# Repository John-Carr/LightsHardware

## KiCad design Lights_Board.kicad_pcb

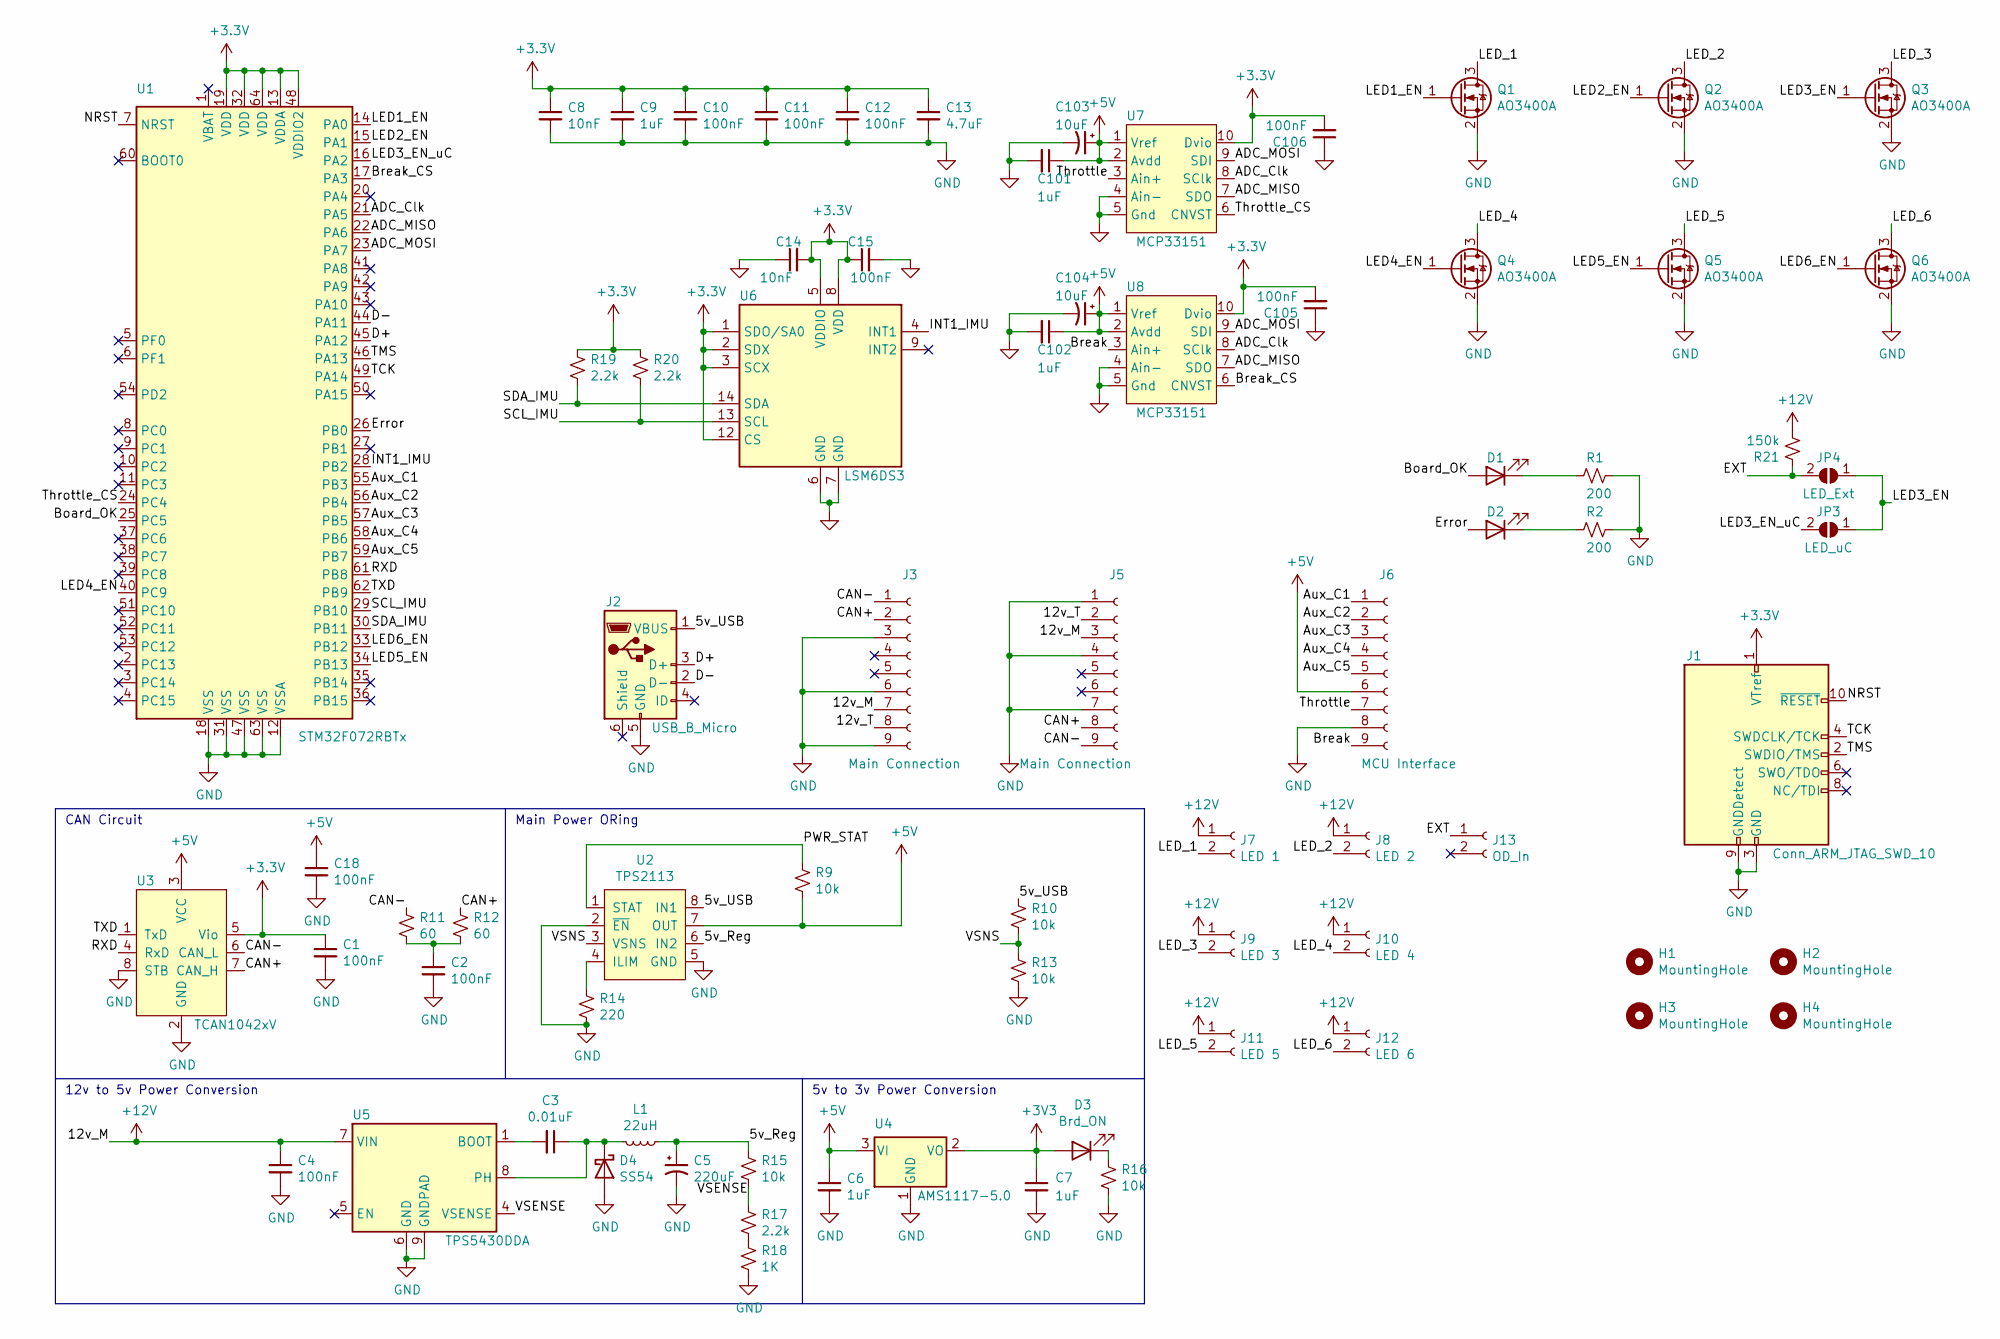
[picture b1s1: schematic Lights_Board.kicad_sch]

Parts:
C1, C2, C4, C10, C11, C12, C15, C18, C105, C106: 100nF; C_0402_1005Metric; LCSC Part C307331
C3: 0.01uF; C_0402_1005Metric; LCSC Part C15195
C5: 220uF; CP_Elec_8x5.4; LCSC Part C3345
C6, C7, C9, C101, C102: 1uF; C_0402_1005Metric; LCSC Part C52923
C8, C14: 10nF; C_0402_1005Metric; LCSC Part C15195
C13: 4.7uF; C_0402_1005Metric; LCSC Part C23733
C103, C104: 10uF; CP_EIA-3216-18_Kemet-A; LCSC Part C7171
D1: Board OK; LED_0805_2012Metric; LCSC Part C2297
D2: Error; LED_0603_1608Metric; LCSC Part C2286
D3: Brd_ON; LED_0805_2012Metric; LCSC Part C2297
D4: SS54; D_SMA; LCSC Part C22452
H1, H2, H3, H4: MountingHole; MountingHole_3.2mm_M3
J1: Conn_ARM_JTAG_SWD_10; PinHeader_2x05_P1.27mm_Vertical_SMD
J2: USB_B_Micro; USB_Micro-B_Molex_47346-0001
J3, J5: Main Connection; Molex_Micro-Fit_3.0_43650-0900_1x09_P3.00mm_Horizontal
J6: MCU Interface; Molex_Micro-Fit_3.0_43650-0900_1x09_P3.00mm_Horizontal
J7: LED 1; Molex_Micro-Fit_3.0_43650-0200_1x02_P3.00mm_Horizontal
J8: LED 2; Molex_Micro-Fit_3.0_43650-0200_1x02_P3.00mm_Horizontal
J9: LED 3; Molex_Micro-Fit_3.0_43650-0200_1x02_P3.00mm_Horizontal
J10: LED 4; Molex_Micro-Fit_3.0_43650-0200_1x02_P3.00mm_Horizontal
J11: LED 5; Molex_Micro-Fit_3.0_43650-0200_1x02_P3.00mm_Horizontal
J12: LED 6; Molex_Micro-Fit_3.0_43650-0200_1x02_P3.00mm_Horizontal
J13: OD_In; Molex_Micro-Fit_3.0_43650-0200_1x02_P3.00mm_Horizontal
JP3: LED_uC; SolderJumper-2_P1.3mm_Open_RoundedPad1.0x1.5mm
JP4: LED_Ext; SolderJumper-2_P1.3mm_Open_RoundedPad1.0x1.5mm
L1: 22uH; L_Panasonic_YFP; LCSC Part C38117
Q1, Q2, Q3, Q4, Q5, Q6: AO3400A; SOT-23; LCSC Part C20917
R1, R2: 200; R_0603_1608Metric; LCSC Part C8218
R9, R10, R13, R15, R16: 10k; R_0603_1608Metric; LCSC Part C25804
R11, R12: 60; R_0603_1608Metric
R14: 220; R_0603_1608Metric; LCSC Part C22962
R17, R19, R20: 2.2k; R_0603_1608Metric; LCSC Part C4190
R18: 1K; R_0603_1608Metric; LCSC Part C21190
R21: 150k; R_0603_1608Metric; LCSC Part C22807
U1: STM32F072RBTx; LQFP-64_10x10mm_P0.5mm
U2: TPS2113; TSSOP-8_4.4x3mm_P0.65mm
U3: TCAN1042xV; SOIC-8
U4: AMS1117-5.0; SOT-223-3_TabPin2; LCSC Part C6186
U5: TPS5430DDA; TI_SO-PowerPAD-8_ThermalVias; LCSC Part C9864
U6: LSM6DS3; LGA-14_3x2.5mm_P0.5mm_LayoutBorder3x4y; LCSC Part C784817
U7, U8: MCP33151; MSOP-10_3x3mm_P0.5mm

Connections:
+5V: C6.1, C18.1, C101.1, C102.1, C103.1, C104.1, J6.6, R9.2, U2.7 (OUT), U3.3 (VCC), U4.3 (VI), U7.1 (Vref), U7.2 (Avdd), U8.1 (Vref), U8.2 (Avdd)
+12V: C4.1, J3.7, J5.3, J7.1, J8.1, J9.1, J10.1, J11.1, J12.1, R21.2, U5.7 (VIN)
/5v_Reg: C5.1, L1.1, R15.1, U2.6 (IN2)
/5v_USB: J2.1 (VBUS), R10.1, U2.8 (IN1)
/12v_T: J3.8, J5.2
/ADC_Clk: U1.21 (PA5), U7.8 (SClk), U8.8 (SClk)
/ADC_MISO: U1.22 (PA6), U7.7 (SDO), U8.7 (SDO)
/ADC_MOSI: U1.23 (PA7), U7.9 (SDI), U8.9 (SDI)
/Aux_C1: J6.1, U1.55 (PB3)
/Aux_C2: J6.2, U1.56 (PB4)
/Aux_C3: J6.3, U1.57 (PB5)
/Aux_C4: J6.4, U1.58 (PB6)
/Aux_C5: J6.5, U1.59 (PB7)
/Board_OK: D1.2 (A), U1.25 (PC5)
/Break: J6.9, U8.3 (Ain+)
/Break_CS: U1.17 (PA3), U8.6 (CNVST)
/CAN+: J3.2, J5.8, R12.1, U3.7 (CAN_H)
/CAN-: J3.1, J5.9, R11.1, U3.6 (CAN_L)
/D+: J2.3 (D+), U1.45 (PA12)
/D-: J2.2 (D-), U1.44 (PA11)
/EXT: J13.1, JP4.2 (B), R21.1
/Error: D2.2 (A), U1.26 (PB0)
/INT1_IMU: U1.28 (PB2), U6.4 (INT1)
/LED1_EN: Q1.1 (G), U1.14 (PA0)
/LED2_EN: Q2.1 (G), U1.15 (PA1)
/LED3_EN: JP3.1 (A), JP4.1 (A), Q3.1 (G)
/LED3_EN_uC: JP3.2 (B), U1.16 (PA2)
/LED4_EN: Q4.1 (G), U1.40 (PC9)
/LED5_EN: Q5.1 (G), U1.34 (PB13)
/LED6_EN: Q6.1 (G), U1.33 (PB12)
/LED_1: J7.2, Q1.3 (D)
/LED_2: J8.2, Q2.3 (D)
/LED_3: J9.2, Q3.3 (D)
/LED_4: J10.2, Q4.3 (D)
/LED_5: J11.2, Q5.3 (D)
/LED_6: J12.2, Q6.3 (D)
/NRST: J1.10 (~RESET), U1.7 (NRST)
/PWR_STAT: R9.1, U2.1 (STAT)
/RXD: U1.61 (PB8), U3.4 (RxD)
/SCL_IMU: R20.2, U1.29 (PB10), U6.13 (SCL)
/SDA_IMU: R19.2, U1.30 (PB11), U6.14 (SDA)
/TCK: J1.4 (SWDCLK/TCK), U1.49 (PA14)
/TMS: J1.2 (SWDIO/TMS), U1.46 (PA13)
/TXD: U1.62 (PB9), U3.1 (TxD)
/Throttle: J6.7, U7.3 (Ain+)
/Throttle_CS: U1.24 (PC4), U7.6 (CNVST)
/VSENSE: R15.2, R17.1, U5.4 (VSENSE)
/VSNS: R10.2, R13.1, U2.3 (VSNS)
GND: C1.2, C2.2, C4.2, C5.2, C6.2, C7.2, C8.2, C9.2, C10.2, C11.2, C12.2, C13.2, C14.1, C15.2, C18.2, C101.2, C102.2, C103.2, C104.2, C105.1, C106.1, D4.2 (A), J1.3 (GND), J1.5 (GND), J1.9 (GNDDetect), J2.5 (GND), J3.3, J3.6, J3.9, J5.1, J5.4, J5.7, J6.8, Q1.2 (S), Q2.2 (S), Q3.2 (S), Q4.2 (S), Q5.2 (S), Q6.2 (S), R1.1, R2.1, R13.2, R14.2, R16.2, R18.2, U1.12 (VSSA), U1.18 (VSS), U1.31 (VSS), U1.47 (VSS), U1.63 (VSS), U2.2 (~EN), U2.5 (GND), U3.2 (GND), U3.8 (STB), U4.1 (GND), U5.6 (GND), U5.9 (GNDPAD), U6.6 (GND), U6.7 (GND), U7.4 (Ain-), U7.5 (Gnd), U8.4 (Ain-), U8.5 (Gnd)
unnamed: C2.1, R11.2, R12.2
unnamed: C3.1, D4.1 (K), L1.2, U5.8 (PH)
unnamed: C3.2, U5.1 (BOOT)
unnamed: D1.1 (K), R1.2
unnamed: D2.1 (K), R2.2
unnamed: D3.1 (K), R16.1
unnamed: R14.1, U2.4 (ILIM)
unnamed: R17.2, R18.1

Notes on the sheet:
5v to 3v Power Conversion
12v to 5v Power Conversion
CAN Circuit
Main Power ORing

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
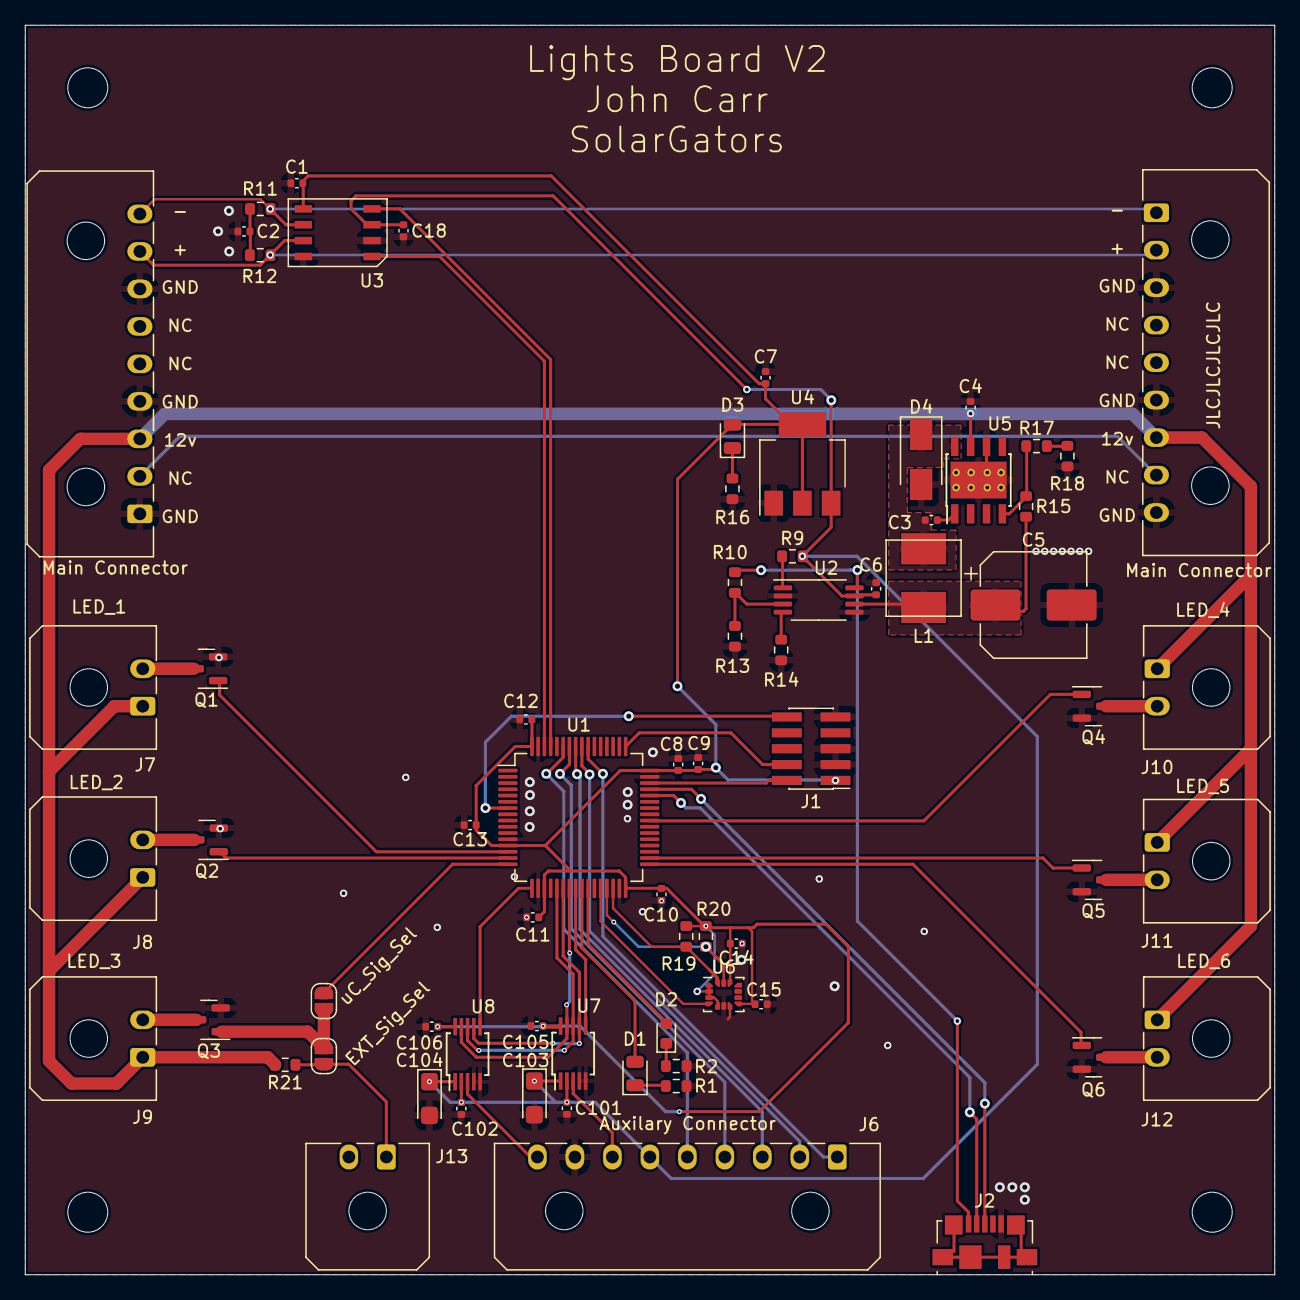
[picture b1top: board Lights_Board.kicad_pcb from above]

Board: 2 copper layers, 100.0 x 100.0 mm, 74 parts (0 on the bottom side), 58 nets.

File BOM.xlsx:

Id | Designator | Footprint | Quantity | Designation | Supplier and ref | Column1 | _1
1 | C15,C16,C12,C11,C10,C4,C2,C1 | C_0402_1005Metric | 8 | 100nF
2 | U6 | InvenSense_QFN-24_4x4mm_P0.5mm | 1 | MPU-6050
3 | R20,R19,R17 | R_0603_1608Metric | 3 | 2.2kÎ©
4 | R18 | R_0603_1608Metric | 1 | 1kÎ©
5 | C17 | C_0402_1005Metric | 1 | 2.2nF
6 | C14,C8 | C_0402_1005Metric | 2 | 10nF
7 | R8,R7,R6,R5,R4,R3 | R_0805_2012Metric | 6 | 200
8 | L1 | L_Vishay_IHLP-2525 | 1 | 22uH
9 | D4 | D_SMA | 1 | SS52
10 | C13 | C_0402_1005Metric | 1 | 4.7uF
11 | C9,C7,C6 | C_0402_1005Metric | 3 | 1uF
12 | JP3 | SolderJumper-2_P1.3mm_Open_RoundedPad1.0x1.5mm | 1 | LED_uC
13 | R21 | R_0603_1608Metric | 1 | 150k
14 | Q7 | SOT-23 | 1 | AO3401A
15 | JP4 | SolderJumper-2_P1.3mm_Open_RoundedPad1.0x1.5mm | 1 | LED_Ext
16 | J13 | Molex_Micro-Fit_3.0_43650-0200_1x02_P3.00mm_Horizontal | 1 | OD_In
17 | H4,H3,H2,H1 | MountingHole_3.2mm_M3 | 4 | MountingHole
18 | U5 | TI_SO-PowerPAD-8_ThermalVias | 1 | TPS5430DDA
19 | U4 | SOT-223-3_TabPin2 | 1 | AMS1117-5.0
20 | U3 | SOIC-8 | 1 | TCAN1042xV
21 | U2 | TSSOP-8_4.4x3mm_P0.65mm | 1 | TPS2113
22 | U1 | LQFP-64_10x10mm_P0.5mm | 1 | STM32F072RBTx
23 | R16,R15,R13,R10,R9 | R_0603_1608Metric | 5 | 10k
24 | R14 | R_0603_1608Metric | 1 | 250
25 | R12,R11 | R_0603_1608Metric | 2 | 60
26 | R2,R1 | R_0603_1608Metric | 2 | 200
27 | Q6,Q5,Q4,Q3,Q2,Q1 | SOT-23 | 6 | AO3400A
28 | JP2 | SolderJumper-2_P1.3mm_Open_RoundedPad1.0x1.5mm | 1 | CAN_3v
29 | JP1 | SolderJumper-2_P1.3mm_Open_RoundedPad1.0x1.5mm | 1 | CAN_5v
30 | J12 | Molex_Micro-Fit_3.0_43650-0200_1x02_P3.00mm_Horizontal | 1 | LED 6
31 | J11 | Molex_Micro-Fit_3.0_43650-0200_1x02_P3.00mm_Horizontal | 1 | LED 5
32 | J10 | Molex_Micro-Fit_3.0_43650-0200_1x02_P3.00mm_Horizontal | 1 | LED 4
33 | J9 | Molex_Micro-Fit_3.0_43650-0200_1x02_P3.00mm_Horizontal | 1 | LED 3
34 | J8 | Molex_Micro-Fit_3.0_43650-0200_1x02_P3.00mm_Horizontal | 1 | LED 2
35 | J7 | Molex_Micro-Fit_3.0_43650-0200_1x02_P3.00mm_Horizontal | 1 | LED 1
36 | J6 | Molex_Micro-Fit_3.0_43650-0900_1x09_P3.00mm_Horizontal | 1 | MCU Interface
37 | J5,J4,J3 | Molex_Micro-Fit_3.0_43650-0900_1x09_P3.00mm_Horizontal | 3 | Main Connection
38 | J2 | USB_Micro-B_Molex_47346-0001 | 1 | USB_B_Micro
39 | J1 | PinHeader_2x05_P1.27mm_Vertical_SMD | 1 | Conn_ARM_JTAG_SWD_10
40 | D3 | LED_0805_2012Metric_Castellated | 1 | Brd_ON
41 | D2 | LED_0603_1608Metric_Castellated | 1 | Error
42 | D1 | LED_0805_2012Metric_Castellated | 1 | Board OK
43 | C5 | CP_Elec_6.3x5.3 | 1 | 220uF
44 | C3 | C_0402_1005Metric | 1 | 0.01uF

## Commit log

2022-02-24 Initial work
2022-06-09 Rev2
2022-06-09 Add docs
2022-06-16 Adding automation
2022-06-16 Remove backups from git
2022-06-16 Revision 2 (#1)
    Features:
    Automation
    New ADC that doesn't kill the uC
    Fixed nmos controlling lights on high side causing LEDs to be dim
    Bugs:
    ADC Requires 1.8v analog supply voltage this board only supplies 5v to the ADC which will kill the IC. Jumpers and LDO required for hotfix.
